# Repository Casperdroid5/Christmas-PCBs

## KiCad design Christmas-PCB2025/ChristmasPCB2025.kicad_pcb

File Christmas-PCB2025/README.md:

# Christmas ball-card 🎄 

This project provides hardware and firmware for an ESP32-C3 based Christmas-themed PCB that controls an array of addressable LEDs and plays Christmas songs via a buzzer. It includes local controls via two buttons, an automatic 6-hour timer, battery monitoring, and as an extra: a WiFi-based configuration interface.

***

## ✨ Features

* **LED Control:** Drives **8 WS2812B (or compatible) addressable RGB LEDs** using the **FastLED** library.
* **Christmas Music:** Plays a selection of classic **Christmas songs** through a dedicated **buzzer**.
* **Timer Functionality:** Features a 6-hour "ON" timer that cycles every 24 hours (this can be toggled on/off by holding button 1).
* **Local Control:** Two physical buttons for easy control of patterns, music, and the timer.
* **WiFi Configuration:** A temporary **Access Point (AP) mode** for changing persistent settings via a simple web interface.
* **Ambient Light Sensing:** Support for an LDR (Light Dependent Resistor) to potentially adjust brightness based on the environment. (not implemented)

***

## 🛠️ Hardware Requirements

The firmware is designed for a custom board based on the **ESP32-C3** microcontroller.

| Component | Pin (GPIO) | Description |
| :--- | :--- | :--- |
| **RGB LED Data** | **3** | Data line for the WS2812B LED strip/array (8 LEDs total). |
| **Buzzer/Speaker** | **10** | Output for playing musical tones. |
| **Button 1** | **4** | Multi-function button (Pattern change / Timer toggle). |
| **Button 2** | **5** | Music control (Play/Stop). |
| **Battery Sense** | **0** | Analog input for battery voltage monitoring. |
| **LDR Pin** | **2** | Analog input for ambient light sensing (Light Dependent Resistor). |

***

## ⚙️ Software Setup & Building

This project is built using the **PlatformIO** ecosystem within Visual Studio Code or as a standalone CLI tool.

### Dependencies

The `platformio.ini` file automatically manages these dependencies:

1.  **Espressif 32 Platform**
2.  **Arduino Framework**
3.  **FastLED** (for controlling the addressable LEDs)

### Build Instructions

1.  Install **PlatformIO** (VS Code extension or CLI).
2.  Open the project folder.
3.  Ensure your environment matches the configuration in `platformio.ini`: `[env:esp32-c3-devkitm-1]`.
4.  Use the PlatformIO commands to build and upload the firmware:
    ```bash
    # Build the project
    pio run
    
    # Upload to the device (assuming it is connected)
    pio run --target upload
    ```

***

## 🕹️ Usage & Controls

The device is controlled primarily through the two onboard buttons.

| Control | Action | Function |
| :--- | :--- | :--- |
| **Button 1 (Short Press)** | Press and release quickly. | **Change LED Pattern:** Cycles through the available light effects. |
| **Button 1 (Long Press)** | Hold for 1 second. | **Toggle 6h Timer:** Enables or disables the automatic 6-hour run timer. |
| **Button 2 (Any Press)** | Press to toggle. | **Play/Stop Songs:** Toggles the Christmas music playback. |
| **Both Buttons** | Hold simultaneously for 1 second. | **Toggle WiFi AP Mode:** Enters the configuration mode for web-based settings. |

***

## 🌐 Configuration (WiFi Access Point Mode)

The device supports over-the-air (OTA) configuration using a temporary WiFi Access Point.

### Entering AP Mode

1.  Press and **hold both Button 1 and Button 2 simultaneously** for approximately two seconds.
2.  The device will enable the Access Point (create a network you can connect to)

### Web Configuration

1.  On a smartphone or computer, search for the new WiFi network created by the device (it will be recognizable by "Kerstbal_NAME".
2.  Connect to the Access Point (your device will likely complain that there is no wifi connection available, connect anyways).
3.  Once connected, you can navigate to `http://192.168.4.1` in your browser (like firefox of chrome)
4.  The web interface will allow you to modify settings stored in the **Christmas card**.

### AP Timeout

For security and power-saving, the WiFi Access Point will automatically **turn off after 5 minutes** (300,000 milliseconds) of inactivity. To re-enable it, repeat the two-button press. Wifi will only work when connected to a USB power source (not using batteries)

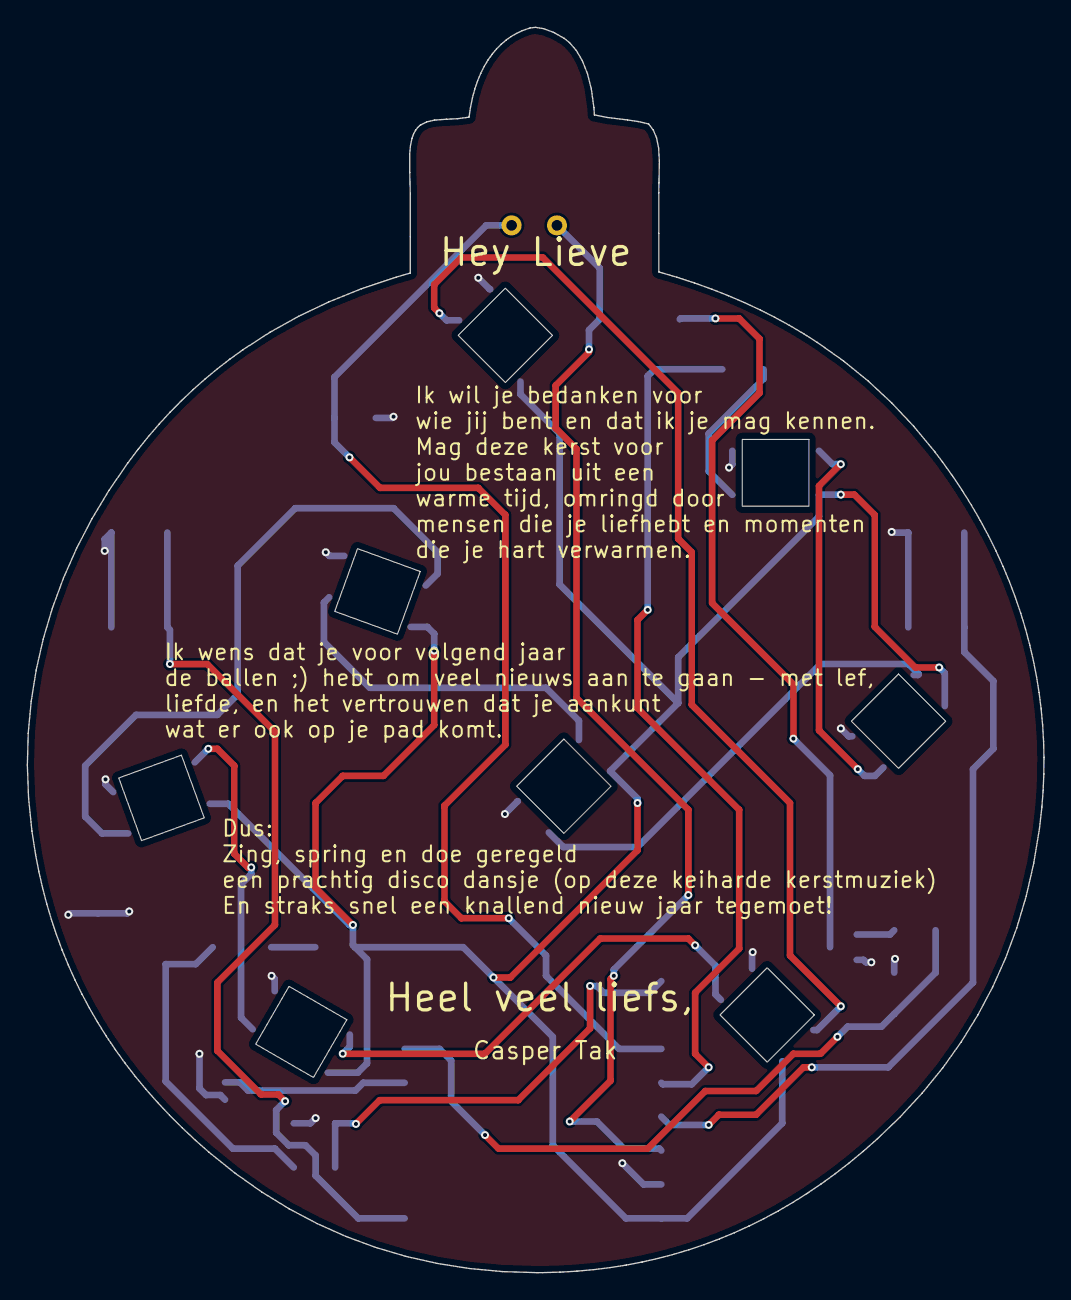
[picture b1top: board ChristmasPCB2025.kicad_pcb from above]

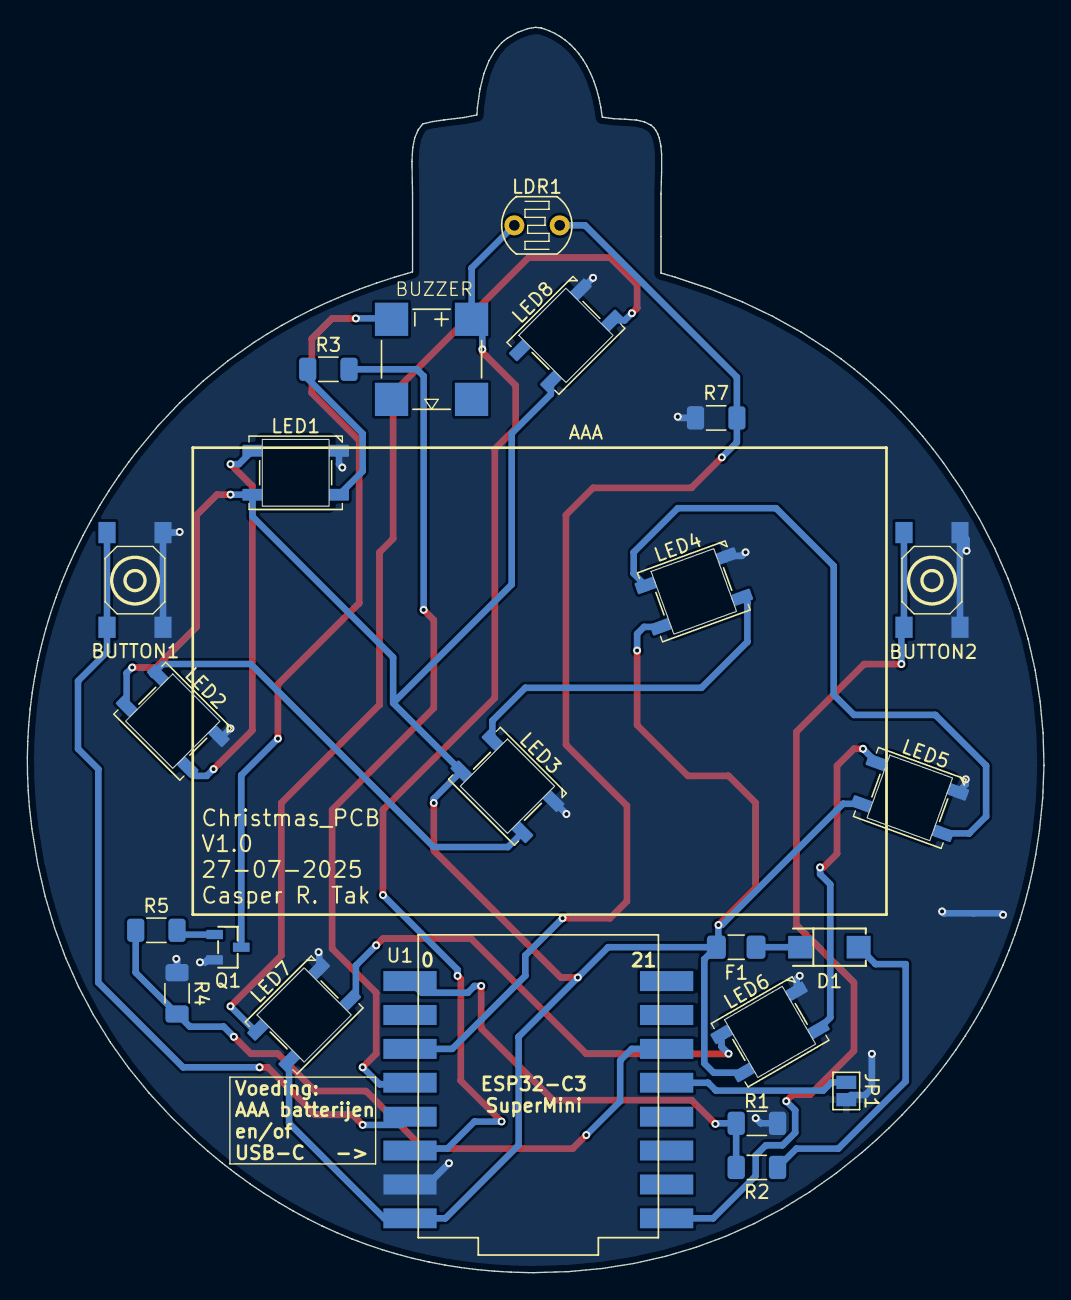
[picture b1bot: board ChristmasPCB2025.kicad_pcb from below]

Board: 2 copper layers, 76.2 x 93.3 mm, 23 parts (23 on the bottom side), 22 nets.

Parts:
BUTTON1, BUTTON2: DTSM-61R-V-T/R; KEY-SMD_4P-L6.2-W6.2-P4.50-LS9.0
D1: 1N5819_C437199; SMA_L4.4-W2.6-LS5.0-RD
F1: Resetable fuse 0.75A; Fuse_1206_3216Metric_Pad1.42x1.75mm_HandSolder
JP1: SolderJumper_2_Open; SolderJumper-2_P1.3mm_Open_Pad1.0x1.5mm
LDR1: LDR07; R_LDR_5.1x4.3mm_P3.4mm_Vertical
LED1, LED2, LED3, LED4, LED5, LED6, LED7, LED8: WS2812B; LED_WS2812B_PLCC4_5.0x5.0mm_P3.2mm
LS1: KSSGK4B16-20
Q1: 2N7002_C306856; SOT-23-3_L2.9-W1.3-P1.90-LS2.4-BR
R1, R2, R4: 10k; R_1206_3216Metric_Pad1.30x1.75mm_HandSolder
R3: 200; R_1206_3216Metric_Pad1.30x1.75mm_HandSolder
R5: 100; R_1206_3216Metric_Pad1.30x1.75mm_HandSolder
R7: 5k; R_1206_3216Metric_Pad1.30x1.75mm_HandSolder
U1: ESP32-C3_SUPERMINI_TH; MODULE_ESP32-C3_SUPERMINI

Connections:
+3V3: LDR1.1, LS1.P, U1.3.3 (3V3)
+5V: F1.1, LED1.1 (VDD), LED2.1 (VDD), LED3.1 (VDD), LED4.1 (VDD), LED5.1 (VDD), LED6.1 (VDD), LED7.1 (VDD), LED8.1 (VDD), U1.5V
BATT_V: R1.1, R2.2, U1.0 (GPIO0)
BUZZ: R4.2, R5.1, U1.10 (GPIO10)
GND: BUTTON1.1, BUTTON1.3, BUTTON2.1, BUTTON2.3, JP1.1 (A), LED1.3 (VSS), LED2.3 (VSS), LED3.3 (VSS), LED4.3 (VSS), LED5.3 (VSS), LED6.3 (VSS), LED7.3 (VSS), LED8.3 (VSS), Q1.2 (S), R1.2, R4.1, R7.2, U1.G (GND)
unnamed: D1.2 (A), R2.1
unnamed: D1.1 (C), F1.2
unnamed: JP1.2 (B), U1.9 (GPIO9)
unnamed: LED1.4 (DIN), R3.1
unnamed: LED1.2 (DOUT), LED2.4 (DIN)
unnamed: LED2.2 (DOUT), LED3.4 (DIN)
unnamed: LED3.2 (DOUT), LED4.4 (DIN)
unnamed: LED4.2 (DOUT), LED5.4 (DIN)
unnamed: LED5.2 (DOUT), LED6.4 (DIN)
unnamed: LED6.2 (DOUT), LED7.4 (DIN)
unnamed: LED7.2 (DOUT), LED8.4 (DIN)
unnamed: LS1.N, Q1.3 (D)
unnamed: Q1.1 (G), R5.2
unnamed: LDR1.2, R7.1, U1.2 (GPIO2)
unnamed: BUTTON1.2, BUTTON1.4, U1.4 (GPIO4)
unnamed: BUTTON2.2, BUTTON2.4, U1.5 (GPIO5)
RGB: R3.2, U1.3 (GPIO3)

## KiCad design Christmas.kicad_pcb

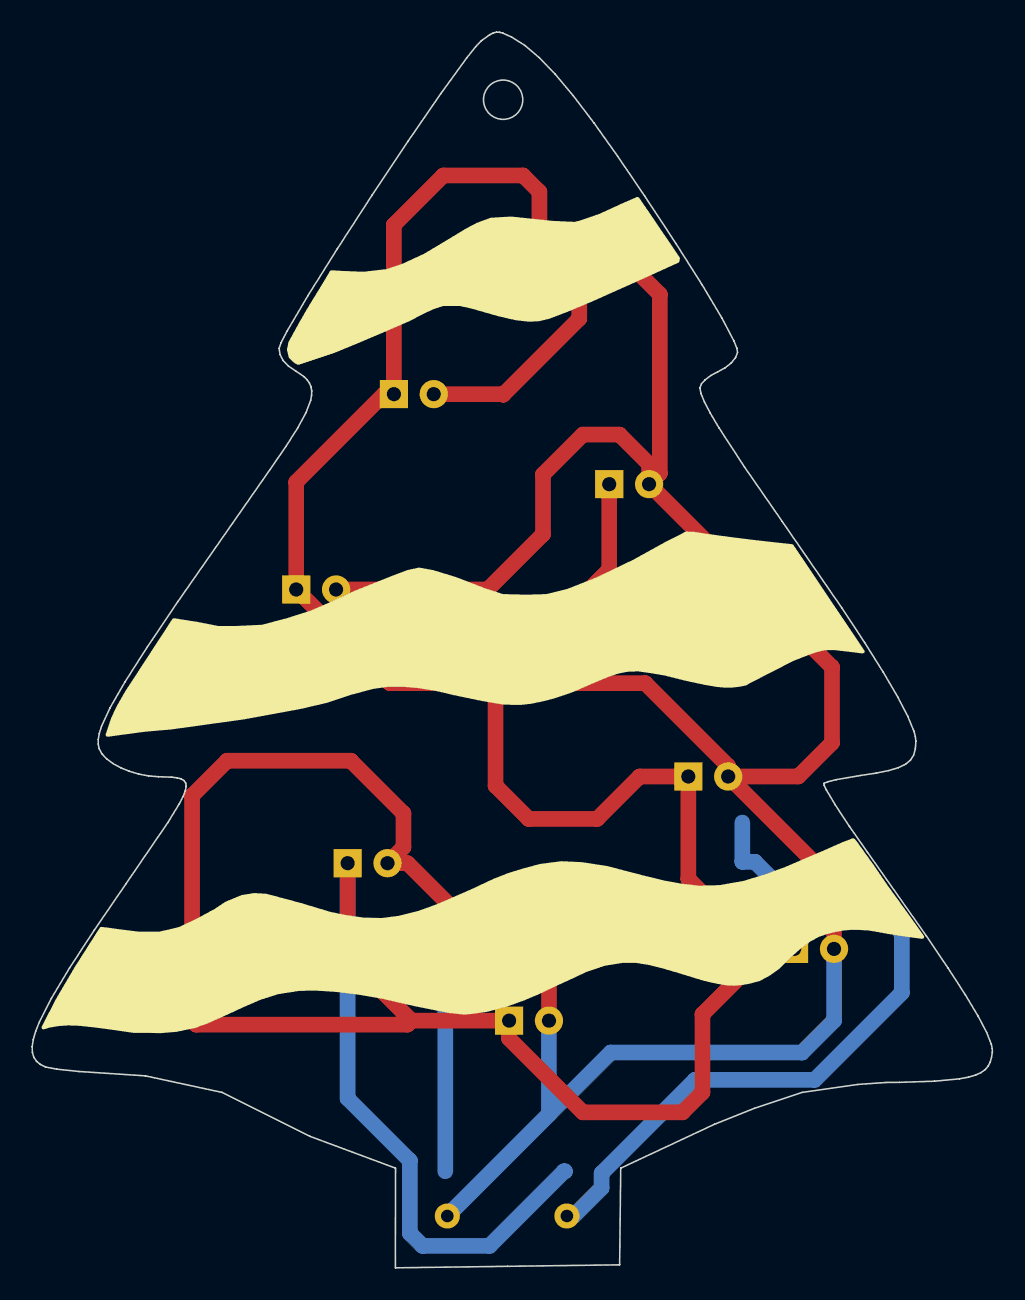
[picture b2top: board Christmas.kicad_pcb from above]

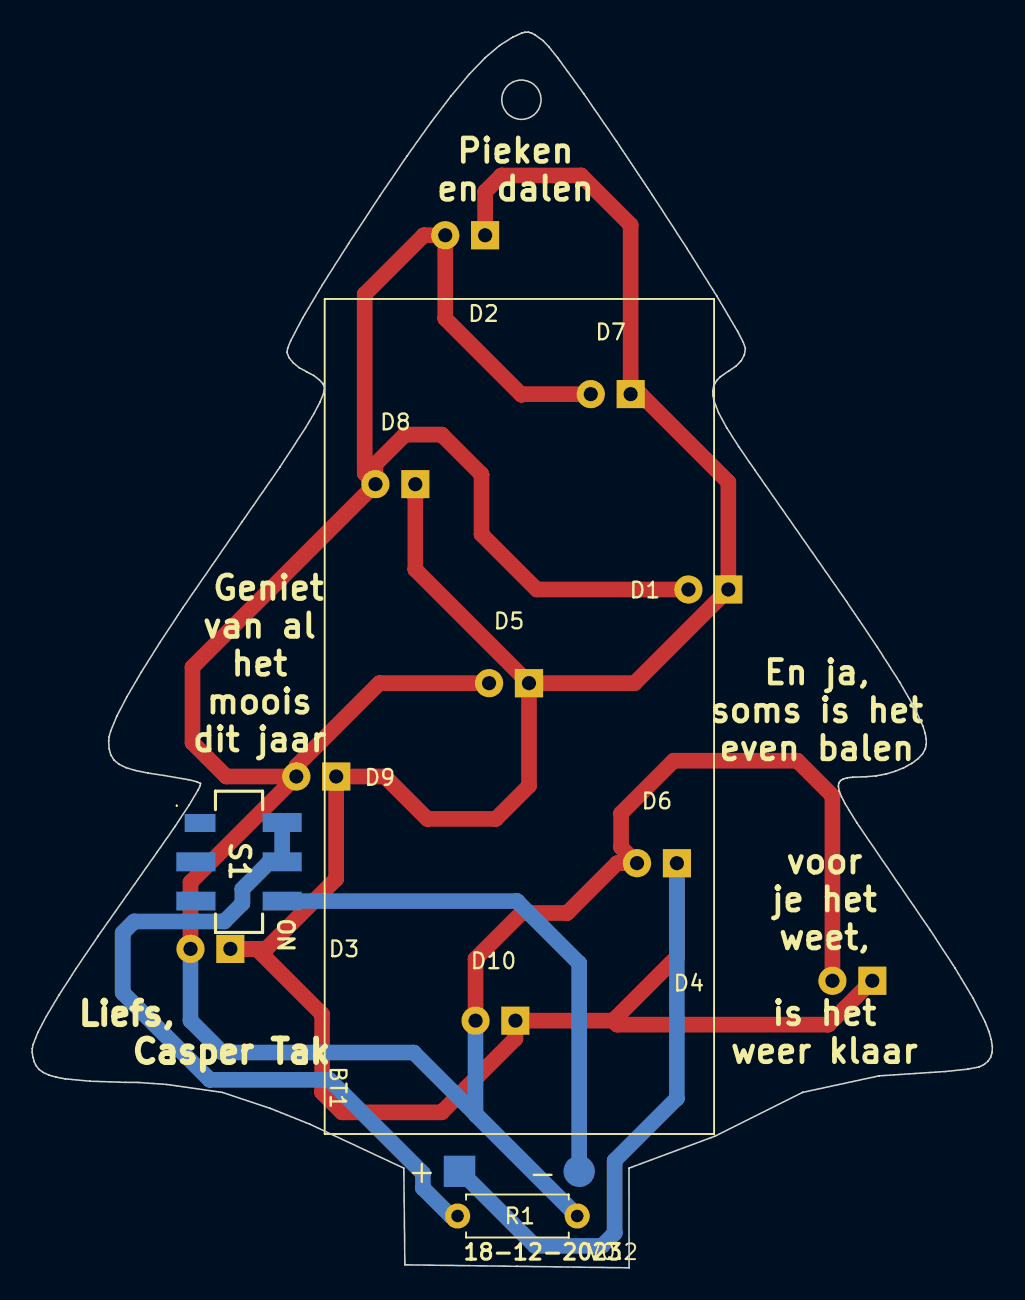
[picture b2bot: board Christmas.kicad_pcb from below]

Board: 2 copper layers, 61.2 x 78.7 mm, 13 parts (3 on the bottom side), 4 nets.

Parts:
BT1: Battery; BatteryHolder_Keystone_2468_2xAAA
D1, D2, D3, D4, D5, D6, D7, D8, D9, D10: LED; LED_D5.0mm_Clear
R1: 0; R_Axial_DIN0207_L6.3mm_D2.5mm_P7.62mm_Horizontal
S1: JS202011SCQN

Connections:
unnamed: BT1.2, S1.4
unnamed: BT1.1, D1.1 (K), D2.1 (K), D3.1 (K), D4.1 (K), D5.1 (K), D6.1 (K), D7.1 (K), D8.1 (K), D9.1 (K), D10.1 (K)
unnamed: D1.2 (A), D2.2 (A), D3.2 (A), D4.2 (A), D5.2 (A), D6.2 (A), D7.2 (A), D8.2 (A), D9.2 (A), D10.2 (A), R1.2
unnamed: R1.1, S1.5, S1.6

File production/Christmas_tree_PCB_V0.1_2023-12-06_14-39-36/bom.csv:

Designator,Footprint,Quantity,Value,LCSC Part #
BT1,BatteryHolder_Keystone_2468_2xAAA,1,Battery,
"D1, D10, D2, D3, D4, D5, D6, D7, D8, D9",LED_D5.0mm_Clear,10,LED,
R1,R_Axial_DIN0207_L6.3mm_D2.5mm_P7.62mm_Horizontal,1,0,
S1,JS202011SCQN,1,JS202011SCQN,

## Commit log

2023-12-06 Added V0.1 to github
2023-12-06 Started wiring V0.1
2023-12-06 Improved wiring aesthetics
2023-12-06 Minor silkscreen improvements
2023-12-06 Minor routing improvements
2023-12-06 final improvements to V0.1 of pcb
    -improved silkscreen
2023-12-06 added production material
2023-12-18 V0.2 of board added
    - added missing power traces from battery box pads
    - improved aesthetics of tracks
    - improved silkscreen text thickness
2023-12-18 Cleanup and battery symbol change
2024-06-06 starting 2024 PCB
2024-06-07 ws2812 leds working with attiny 85 on platform IO
2024-06-07 random colors and brightness setting realised
2024-06-07 brightness bug removed
2024-06-07 song implemented (leds no longer functional somehow, through grounding issues)
2024-06-07 finished code (hardware not testable atm)
2024-06-07 Non blocking code (no more delays)
2024-06-07 formatting improved
2024-06-07 random ledpattern but not when playing musci
2024-12-23 Updated some documentation
2025-05-02 Started code creation for 2025 christmas card!
2025-05-02 Moved to platform IO
2025-05-02 LDR brightness implementation
2025-05-02 added thresholds to brightness levels
2025-05-03 reprogrammed the card with specific christmass tunes and lighting
2025-05-12 started PCB design for christmascard
2025-07-27 removed many unnecessary components
2025-07-27 added new design types
2025-07-27 settled on ornament design
2025-07-27 finished playfull routing
2025-07-27 finished silkscreen
2025-07-27 Design production files
    this was ordered
2025-07-27 fixed documentation error
2025-08-09 working on code and fixed button design error.
2025-08-09 created flashing light paterns and songs (using AI)
2025-08-09 updated songs
2025-08-09 working on the songs
2025-08-10 Found many new christmas songs!
2025-08-10 Added 2026 folder (for next year concepts) and heavily improved 2025 year's code (AI)
2025-08-10 fixed pinout errors
2025-08-10 more lighting paterns and improved button handling
2025-08-10 continuous LED animations
2025-08-10 improved serial output
2025-08-10 V1.0 of code finished
    - 18 Christmas songs implemented
    - 13 lighting effects for leds
    - usb or AAA power detection (to set led max brightness)
    - ambient light detection (but not doing anything with it for now)
2025-08-10 added memory function
    - device now remembers last led and song state and continues after power cut
2025-08-10 working on esp now code
2025-08-10 added total runtime tracking and improved memory function
2025-08-13 added LDR mode
    - 1 pressed for 2 seconds enables/disables ldr functionality
2025-08-13 added readme
2025-11-23 added webinterface (AI generated crap, but works good enough)
